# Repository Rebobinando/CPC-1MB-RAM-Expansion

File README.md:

# CPC 1MB RAM Expansion

## What is this? Why?

Based on the original design from Revaldinho Amstrad CPC RAM Expansion, this design propose a smaller board form factor. This version then, fits into the many expansion boards available up to now.

This allows, as well as the original design, to enjoy 1MB RAM in our CPC. Other sizing as 64Kb or 512Kb extra RAM configuration are achievable through the 4 switches on the top of the board. This development, as well as Revaldinho design, works on a CPC464, CPC664 and CPC6128.

Original design and complete description are available at [Revaldinho Github](https://github.com/revaldinho/cpc_ram_expansion/tree/master/cpc_ram_expansion1mb)

More development details are available in [VadeRetro forum](https://www.va-de-retro.com/foros/viewtopic.php?t=10455)

## Features

Some differences from the original design:

- There is an added voltage regulator added to allow the supply of 3.3V to the CPLD.
- Some capacitors (3x100NF and 2x10uF) and the voltage regulator are SMD form factor to allow smaller size to board.
- CPLD XC9572XL is adopted and preferred because of its better availability in the market compared to XC9572.
- There is a jumper that allows the selection of which voltage we want to supply to the CPLD:
	  * 5V allows to use XC9572 and XC9536.
	  * 3.3V allows to use XC9572XL and XC9536XL.
- 4-Switch 90 degrees are adopted to allow better accessibility once connected to the expansion board.

CPLD programming is fully compatible with original version available at Revaldinho Gitub. Additional non existing versions in Revaldinho Github are available here.

## Bill of materials

|Qty| Component     | Value               |  Package  |
|---|---------------|---------------------|-----------|
| 2 | Capacitor     | 10uF                | SMD C0805 | 
| 3 | Capacitor     | 100nF               | SMD C0805 |
| 1 | Capacitor     | 22pF - 25V Elec     | DIP  4x1.5|
| 1 | Voltage Reg   | AMS1117-3.3         | SOT223    |
| 1 | CPLD          | XC9572XL            | PLCC44    |
| 2 | RAM           | 628512              | DIP       |
| 1 | pin           | 1x7                 | DIP       |
| 1 | pin           | 1x3                 | DIP       |
| 2 | Resistor net  | 5PIN 3.3K           | DIP       |
| 1 | Switch        | 4 bit               | DIP       |
| 1 | MX4 connector | DC3-50P Right Angle | DIP       |
| 2 | Socket        | 32p - Wide          | DIP       |
| 1 | Socket        | PLCC44              | DIP       |

## Board layout

These are the main elements in the top face:

In the bottom face, we will find the SMD components:

And this is the board installed onto the CPC expansion board:

## Warning & Disclaimer
If you want to build yourself, please proceed and read carefully all this information. Bear in mind that all the information in this project is published in good faith and for general information purpose only. I do not make any warranties about the completeness, reliability, and accuracy of this information. Any action you take upon the information you find here, is strictly at your own risk. I will not be liable for any losses and/or damages. 

## Thanks to

- Revaldinho for publishing all his original design information, making it accessible for the whole users community.

- All the users for VadeRetro forum, who supported the initial batch of units.

## Redistribution

All programs and data files in this project are made available under the terms of the [GNU General Public License v3](https://github.com/Rebobinando/CPC-1MB-RAM-Expansion/blob/main/LICENSE)

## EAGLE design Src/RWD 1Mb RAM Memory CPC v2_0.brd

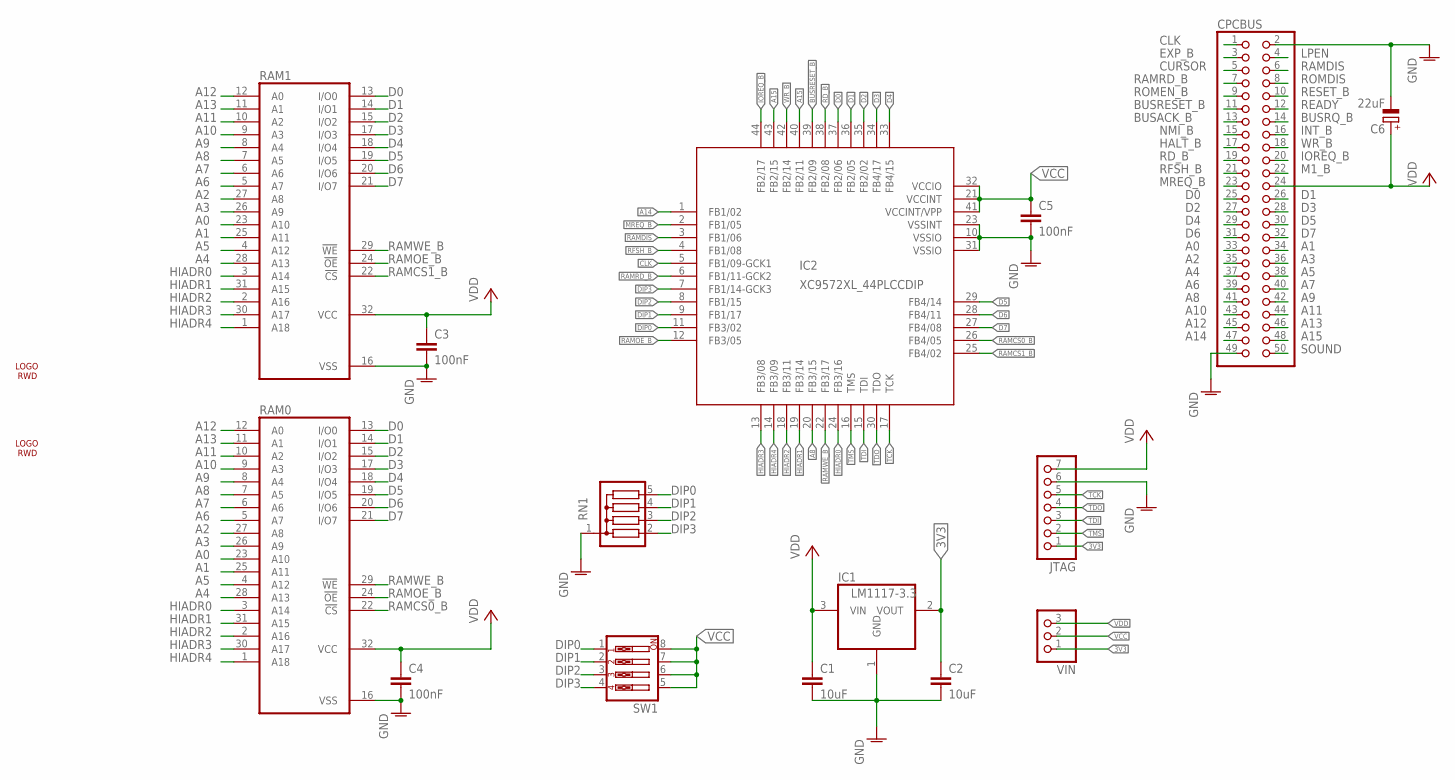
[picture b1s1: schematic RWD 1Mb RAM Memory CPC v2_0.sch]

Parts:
C1, C2: 10uF; RCL_C0805
C3, C4, C5: 100nF; RCL_C0805
C6: 22uF; E2-5
CPCBUS: PINHEAD_PINHD-2X25; PINHEAD_2X25
IC1: LM1117-3.3; BURR-BROWN_SOT223
IC2: XC9572XL_44PLCCDIP; S44
JTAG: PINHD-1X7; 1X07
RAM0, RAM1: MEMORY-HITACHI_628512; MEMORY-HITACHI_DIL32
RN1: G04R; SIL5
SW1: SW_DIP-4; EDG-04
U$1, U$2: LOGO7TOP; LOGO7_SK21
VIN: PINHD-1X3; 1X03

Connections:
3V3: C2.1, IC1.2 (VOUT), JTAG.1, VIN.1
A0: CPCBUS.33, RAM0.23 (A10), RAM1.23 (A10)
A1: CPCBUS.34, RAM0.25 (A11), RAM1.25 (A11)
A2: CPCBUS.35, RAM0.27 (A8), RAM1.27 (A8)
A3: CPCBUS.36, RAM0.26 (A9), RAM1.26 (A9)
A4: CPCBUS.37, RAM0.28 (A13), RAM1.28 (A13)
A5: CPCBUS.38, RAM0.4 (A12), RAM1.4 (A12)
A6: CPCBUS.39, RAM0.5 (A7), RAM1.5 (A7)
A7: CPCBUS.40, RAM0.6 (A6), RAM1.6 (A6)
A8: CPCBUS.41, IC2.20 (FB3/15), RAM0.7 (A5), RAM1.7 (A5)
A9: CPCBUS.42, RAM0.8 (A4), RAM1.8 (A4)
A10: CPCBUS.43, RAM0.9 (A3), RAM1.9 (A3)
A11: CPCBUS.44, RAM0.10 (A2), RAM1.10 (A2)
A12: CPCBUS.45, RAM0.12 (A0), RAM1.12 (A0)
A13: CPCBUS.46, RAM0.11 (A1), RAM1.11 (A1)
A14: CPCBUS.47, IC2.1 (FB1/02)
A15: CPCBUS.48, IC2.40 (FB2/11), IC2.43 (FB2/15)
AGND: C1.2, C2.2, C3.2, C4.2, C5.2, C6.-, CPCBUS.2, CPCBUS.49, IC1.1 (GND), IC2.10 (VSSIO), IC2.23 (VSSINT), IC2.31 (VSSIO), JTAG.6, RAM0.16 (VSS), RAM1.16 (VSS), RN1.1
BUSACK_B: CPCBUS.13
BUSRESET_B: CPCBUS.11, IC2.39 (FB2/09)
BUSRQ_B: CPCBUS.14
CLK: CPCBUS.1, IC2.5 (FB1/09-GCK1)
CURSOR: CPCBUS.5
D0: CPCBUS.25, IC2.37 (FB2/06), RAM0.13 (I/O0), RAM1.13 (I/O0)
D1: CPCBUS.26, IC2.36 (FB2/05), RAM0.14 (I/O1), RAM1.14 (I/O1)
D2: CPCBUS.27, IC2.35 (FB2/02), RAM0.15 (I/O2), RAM1.15 (I/O2)
D3: CPCBUS.28, IC2.34 (FB4/17), RAM0.17 (I/O3), RAM1.17 (I/O3)
D4: CPCBUS.29, IC2.33 (FB4/15), RAM0.18 (I/O4), RAM1.18 (I/O4)
D5: CPCBUS.30, IC2.29 (FB4/14), RAM0.19 (I/O5), RAM1.19 (I/O5)
D6: CPCBUS.31, IC2.28 (FB4/11), RAM0.20 (I/O6), RAM1.20 (I/O6)
D7: CPCBUS.32, IC2.27 (FB4/08), RAM0.21 (I/O7), RAM1.21 (I/O7)
DIP0: IC2.11 (FB3/02), RN1.5, SW1.1
DIP1: IC2.9 (FB1/17), RN1.4, SW1.2
DIP2: IC2.8 (FB1/15), RN1.3, SW1.3
DIP3: IC2.7 (FB1/14-GCK3), RN1.2, SW1.4
EXP_B: CPCBUS.3
HALT_B: CPCBUS.17
HIADR0: IC2.24 (FB3/16), RAM0.3 (A14), RAM1.3 (A14)
HIADR1: IC2.19 (FB3/14), RAM0.31 (A15), RAM1.31 (A15)
HIADR2: IC2.18 (FB3/11), RAM0.2 (A16), RAM1.2 (A16)
HIADR3: IC2.13 (FB3/08), RAM0.30 (A17), RAM1.30 (A17)
HIADR4: IC2.14 (FB3/09), RAM0.1 (A18), RAM1.1 (A18)
INT_B: CPCBUS.16
IOREQ_B: CPCBUS.20, IC2.44 (FB2/17)
LPEN: CPCBUS.4
M1_B: CPCBUS.22
MREQ_B: CPCBUS.23, IC2.2 (FB1/05)
NMI_B: CPCBUS.15
RAMCS0_B: IC2.26 (FB4/05), RAM0.22 (!CS)
RAMCS1_B: IC2.25 (FB4/02), RAM1.22 (!CS)
RAMDIS: CPCBUS.6, IC2.3 (FB1/06)
RAMOE_B: IC2.12 (FB3/05), RAM0.24 (!OE), RAM1.24 (!OE)
RAMRD_B: CPCBUS.7, IC2.6 (FB1/11-GCK2)
RAMWE_B: IC2.22 (FB3/17), RAM0.29 (!WE), RAM1.29 (!WE)
RD_B: CPCBUS.19, IC2.38 (FB2/08)
READY: CPCBUS.12
RESET_B: CPCBUS.10
RFSH_B: CPCBUS.21, IC2.4 (FB1/08)
ROMDIS: CPCBUS.8
ROMEN_B: CPCBUS.9
SOUND: CPCBUS.50
TCK: IC2.17 (TCK), JTAG.5
TDI: IC2.15 (TDI), JTAG.3
TDO: IC2.30 (TDO), JTAG.4
TMS: IC2.16 (TMS), JTAG.2
VCC: C5.1, IC2.21 (VCCINT), IC2.32 (VCCIO), IC2.41 (VCCINT/VPP), SW1.5, SW1.6, SW1.7, SW1.8, VIN.2
VDD: C1.1, C3.1, C4.1, C6.+, CPCBUS.24, IC1.3 (VIN), JTAG.7, RAM0.32 (VCC), RAM1.32 (VCC), VIN.3
WR_B: CPCBUS.18, IC2.42 (FB2/14)

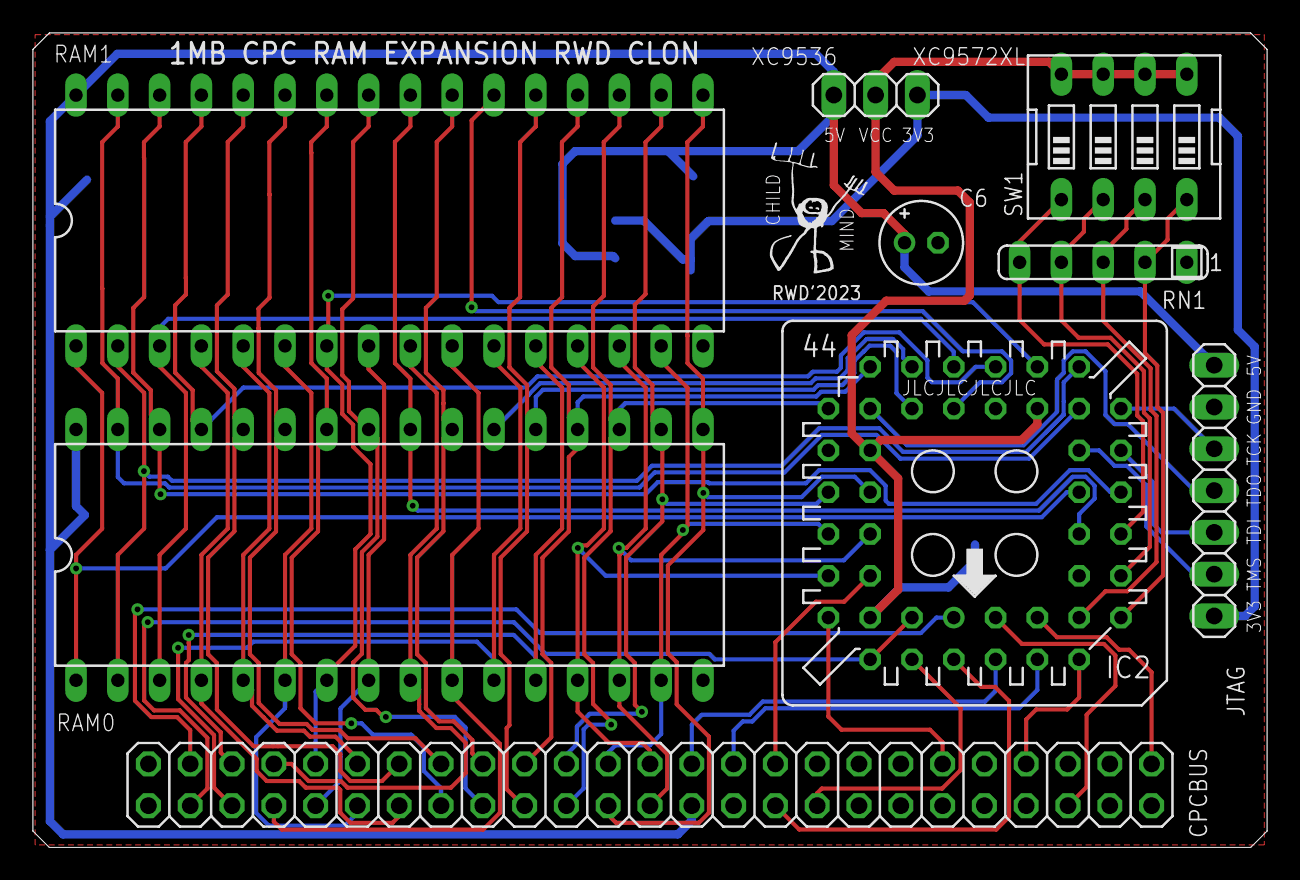
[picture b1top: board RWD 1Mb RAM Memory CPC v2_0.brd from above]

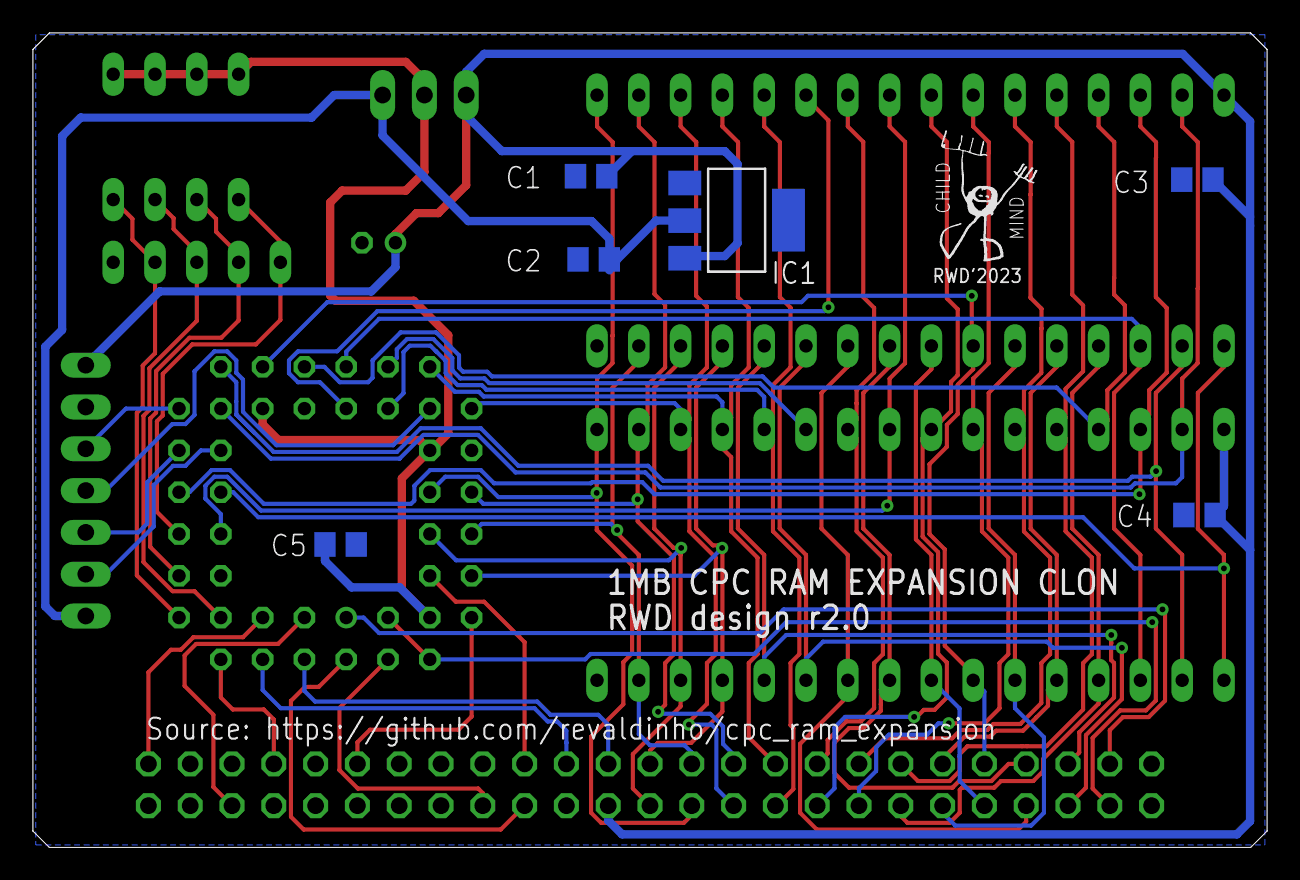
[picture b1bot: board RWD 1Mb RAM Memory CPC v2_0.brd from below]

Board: 2 copper layers, 75.0 x 49.5 mm, 17 parts (7 on the bottom side), 54 nets.

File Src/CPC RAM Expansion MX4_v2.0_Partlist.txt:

Partlist

Exported from RWD 1Mb RAM Memory CPC v2_0.sch at 16/07/2023 1:42

EAGLE Version 8.6.0 Copyright (c) 1988-2018 Autodesk, Inc.

Assembly variant: 

Part     Value              Device                Package              

C1       10uF               RCL_C-EUC0805         RCL_C0805            
C2       10uF               RCL_C-EUC0805         RCL_C0805            
C3       100nF              RCL_C-EUC0805         RCL_C0805            
C4       100nF              RCL_C-EUC0805         RCL_C0805            
C5       100nF              RCL_C-EUC0805         RCL_C0805            
C6       22uF               CPOL-EUE2-5           E2-5                 
CPCBUS                      PINHEAD_PINHD-2X25    PINHEAD_2X25         
IC1      LM1117-3.3         BURR-BROWN_REG1117    BURR-BROWN_SOT223    
IC2      XC9572XL_44PLCCDIP XC9572XL_44PLCCDIP    S44                  
JTAG                        PINHD-1X7             1X07                 
RAM0                        MEMORY-HITACHI_628512 MEMORY-HITACHI_DIL32 
RAM1                        MEMORY-HITACHI_628512 MEMORY-HITACHI_DIL32 
RN1      5x10K              G04R                  SIL5                 
SW1                         SW_DIP-4              EDG-04               
VIN                         PINHD-1X3             1X03
